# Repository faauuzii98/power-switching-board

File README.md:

# power-switching-board
Power Switching board for Lippo battery and Orientation Circuit

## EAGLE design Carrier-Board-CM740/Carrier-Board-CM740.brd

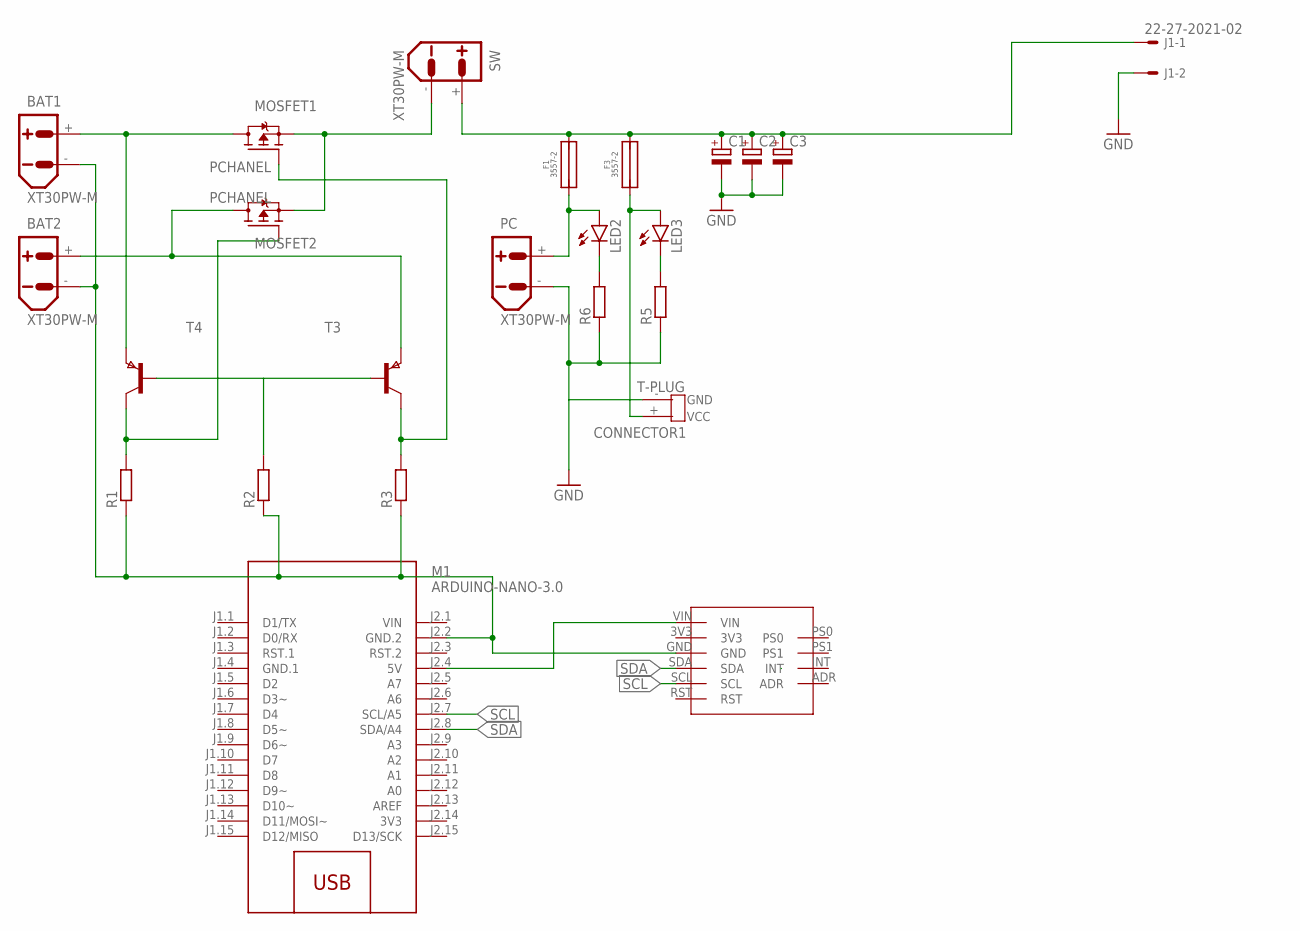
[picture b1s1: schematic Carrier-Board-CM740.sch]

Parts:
BAT1, BAT2: XT30PW-M
C1, C2, C3: CPOL-EU150CLZ-1014; 150CLZ-1014
CONNECTOR1: T-PLUG
F1, F3: 3557-2
J1: 22-27-2021-02; 6410-02
LED2, LED3: LEDCHIP-LED0805; CHIP-LED0805
M1: ARDUINO-NANO-3.0
MOSFET1, MOSFET2: PCHANEL; TO252
PC: XT30PW-M
R1, R2, R3: R-EU_R1206; R1206
R5, R6: R-EU_M0805; M0805
SW: XT30PW-M
T3, T4: PNPSOT23; SOT-23
U$1: BNO055_BNO055

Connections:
3V3: M1.J2.14 (3V3)
GND: BAT1.-, BAT2.-, C1.-, C2.-, C3.-, CONNECTOR1.- (GND), J1.2, M1.J2.2 (GND.2), PC.-, R1.1, R2.1, R3.1, R5.1, R6.1, U$1.GND
GND.1: M1.J1.4 (GND.1)
unnamed: BAT1.+, MOSFET1.3 (D), T4.2 (E)
unnamed: MOSFET2.1 (G), R1.2, T4.1 (C)
unnamed: R2.2, T3.3 (B), T4.3 (B)
unnamed: F1.1, F1.2 (1), LED2.A, PC.+
unnamed: M1.J2.4 (5V), U$1.VIN
unnamed: C1.+, C2.+, C3.+, F1.3 (2), F1.4 (2), F3.3 (2), F3.4 (2), J1.1, SW.+
unnamed: MOSFET1.1 (G), R3.2, T3.1 (C)
unnamed: BAT2.+, MOSFET2.3 (D), T3.2 (E)
unnamed: LED2.C, R6.2
unnamed: MOSFET1.2 (S), MOSFET2.2 (S), SW.-
unnamed: LED3.C, R5.2
SCL: M1.J2.7 (SCL/A5), U$1.SCL
SDA: M1.J2.8 (SDA/A4), U$1.SDA
VCC: CONNECTOR1.+ (VCC), F3.1, F3.2 (1), LED3.A
VIN: M1.J2.1 (VIN)

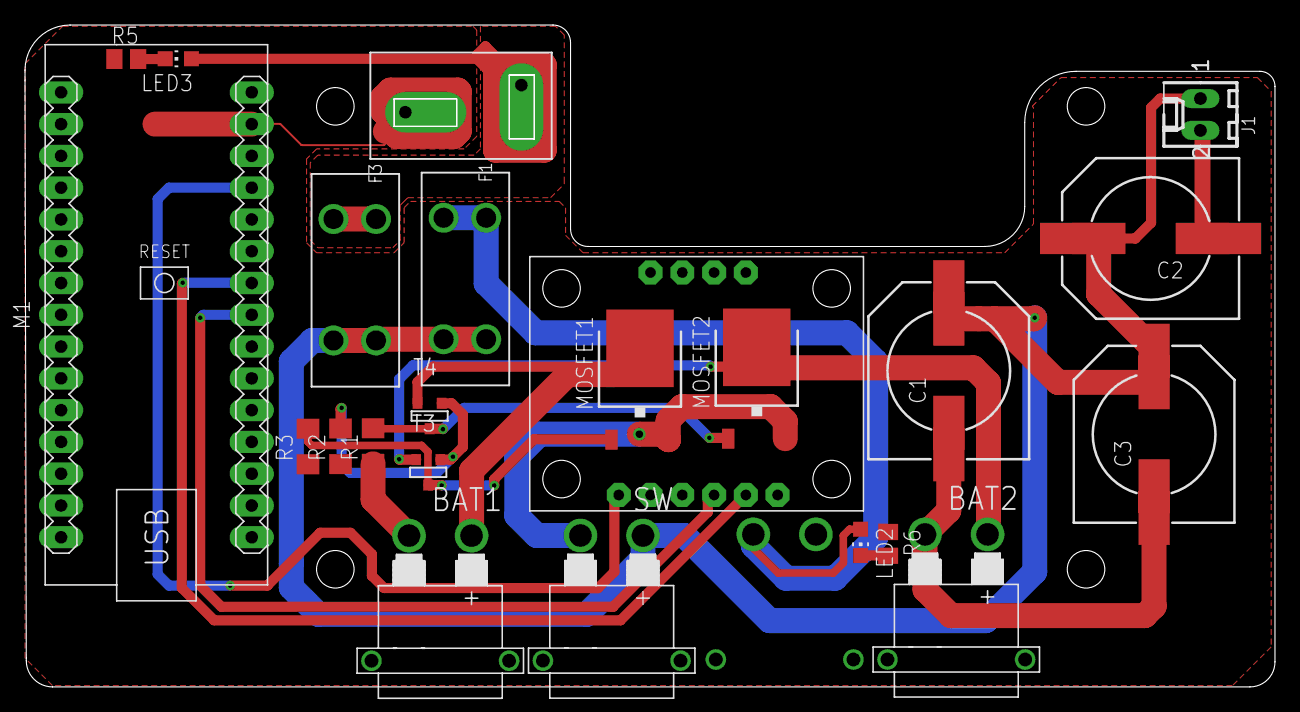
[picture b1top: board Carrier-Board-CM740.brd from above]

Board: 2 copper layers, 99.9 x 52.9 mm, 24 parts (1 on the bottom side), 15 nets.

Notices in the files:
parts and their libraries:
diy-modules: Released under the Creative Commons Attribution 4.0 International License: http://creativecommons.org/licenses/by/4.0
